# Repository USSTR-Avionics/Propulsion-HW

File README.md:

# Propulsion-HW
Electrical Hardware for the Propulsion team, for test firing the hybrid engine

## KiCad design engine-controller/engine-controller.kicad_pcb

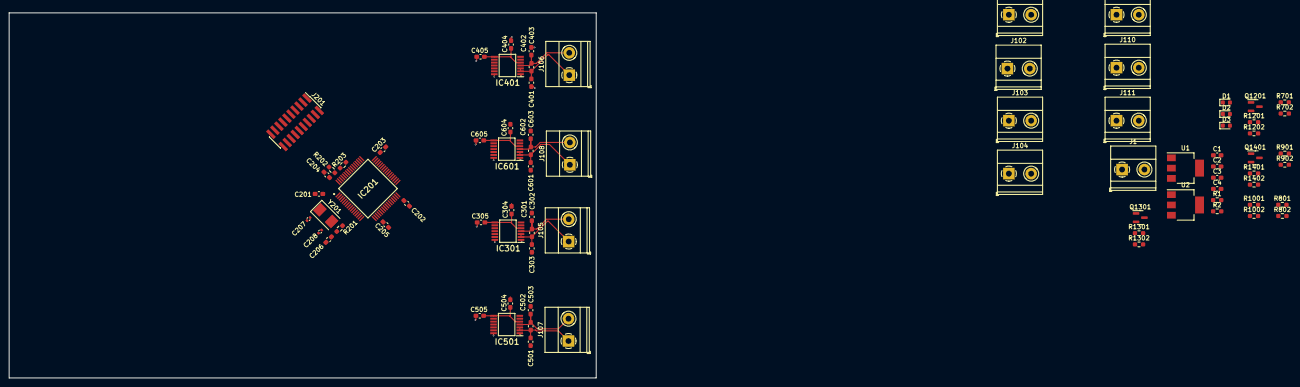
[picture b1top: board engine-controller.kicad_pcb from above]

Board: 2 copper layers, 131.4 x 81.7 mm, 78 parts (0 on the bottom side), 47 nets.

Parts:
C1, C3: 10u; C_0603_1608Metric_Pad1.08x0.95mm_HandSolder
C2, C4: 22u; C_0603_1608Metric_Pad1.08x0.95mm_HandSolder
C201, C202, C203, C204, C205, C206, C301, C304, C305, C402, C404, C405, C502, C504, C505, C602, C604, C605: 0.1u; C_0603_1608Metric_Pad1.08x0.95mm_HandSolder
C207, C208: 30p; C_0402_1005Metric
C302, C303, C401, C403, C501, C503, C601, C603: 0.01u; C_0603_1608Metric_Pad1.08x0.95mm_HandSolder
D1, D2: LED; LED_0603_1608Metric
D3: D; D_0603_1608Metric
IC201: STM32F103RBT6; QFP50P1200X1200X160-64N
IC301, IC401, IC501, IC601: MAX31856MUD+; SOP65P640X110-14N
J1, J101, J102, J103, J104, J105, J106, J107, J108, J109, J110, J111: Screw_Terminal_01x02; TerminalBlock_Phoenix_MKDS-1,5-2_1x02_P5.00mm_Horizontal
J201: Conn_ARM_JTAG_SWD_20; PinHeader_2x10_P1.27mm_Vertical_SMD
Q1201, Q1301, Q1401: 2N7002E; SOT-23
R1, R2, R701, R801, R901, R1001: 1k; R_0603_1608Metric_Pad0.98x0.95mm_HandSolder
R201, R203: 0; R_0603_1608Metric_Pad0.98x0.95mm_HandSolder
R202: 10k; R_0603_1608Metric_Pad0.98x0.95mm_HandSolder
R702, R802, R902, R1002: 150; R_0603_1608Metric_Pad0.98x0.95mm_HandSolder
R1201, R1301, R1401: 330; R_0603_1608Metric_Pad0.98x0.95mm_HandSolder
R1202, R1302, R1402: 1M; R_0603_1608Metric_Pad0.98x0.95mm_HandSolder
U1: AZ1117-3.3; SOT-223
U2: AZ1117-5.0; SOT-223
Y201: 8MHz; Crystal_SMD_5032-2Pin_5.0x3.2mm

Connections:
+3.3V: C2.1, C201.1, C202.1, C203.1, C204.1, C205.1, C206.1, C304.1, C305.1, C404.1, C405.1, C504.1, C505.1, C604.1, C605.1, D2.2 (A), IC201.1 (VBAT), IC201.19 (VDD_4), IC201.32 (VDD_1), IC201.48 (VDD_2), IC201.64 (VDD_3), IC301.5 (AVDD), IC301.8 (DVDD), IC401.5 (AVDD), IC401.8 (DVDD), IC501.5 (AVDD), IC501.8 (DVDD), IC601.5 (AVDD), IC601.8 (DVDD), J201.2 (VCC/NC), R201.1, R203.2, U1.2 (VO)
+5V: C4.1, D1.2 (A), J101.2, J102.2, J103.2, J104.2, U2.2 (VO)
/PT0/4-20mA-IN: J101.1, R701.1
/PT0/4-20mA-OUT: IC201.8 (PC0), R701.2, R702.1
/PT1/4-20mA-IN: J102.1, R801.1
/PT1/4-20mA-OUT: IC201.9 (PC1), R801.2, R802.1
/PT2/4-20mA-IN: J103.1, R901.1
/PT2/4-20mA-OUT: IC201.10 (PC2), R901.2, R902.1
/PT3/4-20mA-IN: J104.1, R1001.1
/PT3/4-20mA-OUT: IC201.11 (PC3), R1001.2, R1002.1
/STM32/BOOT0: IC201.60 (BOOT0), R202.2, R203.1
/STM32/JTDI: IC201.50 (PA15), J201.5 (TDI)
/STM32/JTDO: IC201.55 (PB3), J201.13 (TDO/SWO)
/STM32/PB6: IC201.58 (PB6), IC601.9 (~CS)
/STM32/PB7: IC201.59 (PB7), IC501.9 (~CS)
/STM32/PB8: IC201.61 (PB8), IC401.9 (~CS)
/STM32/PB9: IC201.62 (PB9), IC301.9 (~CS)
/STM32/SPI1_MISO: IC201.22 (PA6), IC301.11 (SDO), IC401.11 (SDO), IC501.11 (SDO), IC601.11 (SDO)
/STM32/SPI1_MOSI: IC201.23 (PA7), IC301.12 (SDI), IC401.12 (SDI), IC501.12 (SDI), IC601.12 (SDI)
/STM32/SPI1_SCK: IC201.21 (PA5), IC301.10 (SCK), IC401.10 (SCK), IC501.10 (SCK), IC601.10 (SCK)
/STM32/SWCLK: IC201.49 (PA14), J201.9 (TCK/SWDCLK)
/STM32/SWDIO: IC201.46 (PA13), J201.7 (TMS/SWDIO)
/STM32/TIM3_CH1: IC201.37 (PC6), R1201.1
/STM32/TIM3_CH2: IC201.38 (PC7), R1301.1
/STM32/TIM3_CH3: IC201.39 (PC8), R1401.1
/Switch0/VALVE-: J109.1, Q1201.3 (D)
/Switch1/VALVE-: J110.1, Q1301.3 (D)
/Switch2/VALVE-: J111.1, Q1401.3 (D)
/TC0/T+: C301.2, C302.1, IC301.4 (T+), J105.2
/TC0/T-: C301.1, C303.1, IC301.2 (BIAS), IC301.3 (T-), J105.1
/TC1/T+: C402.2, C403.1, IC401.4 (T+), J106.2
/TC1/T-: C401.1, C402.1, IC401.2 (BIAS), IC401.3 (T-), J106.1
/TC2/T+: C502.2, C503.1, IC501.4 (T+), J107.2
/TC2/T-: C501.1, C502.1, IC501.2 (BIAS), IC501.3 (T-), J107.1
/TC3/T+: C602.2, C603.1, IC601.4 (T+), J108.2
/TC3/T-: C601.1, C602.1, IC601.2 (BIAS), IC601.3 (T-), J108.1
GND: C1.2, C2.2, C3.2, C4.2, C201.2, C202.2, C203.2, C204.2, C205.2, C206.2, C207.2, C208.2, C302.2, C303.2, C304.2, C305.2, C401.2, C403.2, C404.2, C405.2, C501.2, C503.2, C504.2, C505.2, C601.2, C603.2, C604.2, C605.2, IC201.12 (VSSA), IC201.18 (VSS_4), IC201.31 (VSS_1), IC201.47 (VSS_2), IC201.63 (VSS_3), IC301.1 (AGND), IC301.14 (DGND), IC401.1 (AGND), IC401.14 (DGND), IC501.1 (AGND), IC501.14 (DGND), IC601.1 (AGND), IC601.14 (DGND), J1.2, J201.4 (GND), J201.6 (GND), J201.8 (GND), J201.10 (GND), J201.12 (GND), J201.14 (GND), J201.16 (GND), J201.18 (GND), J201.20 (GND), Q1201.2 (S), Q1301.2 (S), Q1401.2 (S), R1.1, R2.1, R202.1, R702.2, R802.2, R902.2, R1002.2, R1202.1, R1302.1, R1402.1, U1.1 (GND), U2.1 (GND)
unnamed: D1.1 (K), R1.2
unnamed: D2.1 (K), R2.2
unnamed: D3.2 (A), J1.1
unnamed: C207.1, IC201.5 (OSC_IN), Y201.1
unnamed: C208.1, IC201.6 (OSC_OUT), Y201.2
unnamed: IC201.13 (VDDA), R201.2
unnamed: Q1201.1 (G), R1201.2, R1202.2
unnamed: Q1301.1 (G), R1301.2, R1302.2
unnamed: Q1401.1 (G), R1401.2, R1402.2
VCC: C1.1, C3.1, D3.1 (K), J109.2, J110.2, J111.2, U1.3 (VI), U2.3 (VI)

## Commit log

2023-11-22 bare bones stm32
2023-11-22 inital TCs
2023-11-22 added 4-20mA sense circuit
2023-11-24 added switches
2023-11-25 initial layout
